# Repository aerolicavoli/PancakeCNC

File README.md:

# PancakeCNC

A fully custom, pancake-printing CNC platform. This repository collects the mechanical CAD, controller electronics, firmware, ground station tooling, and reference simulations that work together to lay down batter in precise paths.

## Table of Contents
- [Project Overview](#project-overview)
- [Repository Layout](#repository-layout)
- [Mechanical Platform](#mechanical-platform)
- [Electronics and PCB](#electronics-and-pcb)
- [Firmware (`Pancake_esp`)](#firmware-pancake_esp)
- [Ground Station Tools](#ground-station-tools)
- [Simulation & Analysis](#simulation--analysis)
- [Design Documentation](#design-documentation)
- [Command & Telemetry Protocol](#command--telemetry-protocol)
- [Development Environment](#development-environment)
- [License](#license)

## Project Overview
PancakeCNC is a learning platform for end-to-end mechatronics: mechanical design, PCB layout, embedded firmware, networking, and motion control. The goal is to dispense pancake batter using precise CNC motion profiles driven from a custom controller and cloud-connected command stream.

## Repository Layout
```
ControllerPCB/   KiCad project files for the controller board and manufacturing assets.
DesignDocs/      Engineering notes, diagrams, and BOMs.
GroundStation/   Python-based tooling for sending CNC commands and replaying G-code.
PancakeSim/      MATLAB scripts for kinematic studies and controller validation.
Pancake_esp/     ESP-IDF firmware for the ESP32-S3 based controller.
```

## Mechanical Platform
Motion is handled by a double-jointed planar arm that provides two rotational degrees of freedom so the dispenser can reach any point in the intended print envelope. Batter is metered with a peristaltic pump mounted at the arm's end effector.

The printable CAD for the hinges and pump assembly is currently tracked outside this repository; the focus here is on the control stack that drives the mechanism.

## Electronics and PCB
The `ControllerPCB` directory captures the KiCad design for the controller enclosure. Highlights include:

- ESP32-S3 compute module, GPIO breakout, and headers that feed external step/dir motor drivers sourced from the BOM.
- Power conditioning and 5 V level shifting for peripheral interfaces.
- Ready-to-fabricate assets: schematic (`ControllerPCB.kicad_sch`), layout (`ControllerPCB.kicad_pcb`), and generated BOM/gerbers.

## Firmware (`Pancake_esp`)
Firmware is built with ESP-IDF and lives under `Pancake_esp/`. Key modules:

- **Command Handling** (`CommandHandler.*`, `CNCOpCodes.h`): parses high-level instructions into motion primitives.
- **Motion Control** (`MotorControl.*`, `StepperMotor.*`, `TrapezoidalJog.*`, `ArchimedeanSpiral.*`): generates coordinated movements for the S0/S1 axes and pump.
- **Networking & Telemetry** (`InfluxDBCmdAndTlm.*`, `Telemetry.*`, `WifiHandler.*`): streams commands from InfluxDB and publishes runtime state.
- **Safety & UI** (`Safety.*`, `UI.*`): implements interlocks and emergency stop logic. A dedicated human interface is still a work in progress—commands flow through the InfluxDB bridge today.

To build the firmware you will need the ESP-IDF toolchain (v5.x recommended). After configuring credentials in `sdkconfig`/`Secret.h`, standard `idf.py build flash monitor` targets apply.

### Viewing ESP logs over the flash serial port (macOS)
The firmware keeps ESP-IDF logging active on the default serial sink, so anything emitted with `ESP_LOG*` can be viewed on the same USB serial device used for flashing.

1. List serial devices:
   ```bash
   ls /dev/cu.usb*
   ```
2. Open a monitor (replace the port with your device):
   ```bash
   idf.py -p /dev/cu.usbmodemXXXX monitor
   ```
   If you are outside an ESP-IDF shell, a simple fallback is:
   ```bash
   screen /dev/cu.usbmodemXXXX 115200
   ```
3. Exit monitor:
   - `idf.py monitor`: press `Ctrl+]`
   - `screen`: press `Ctrl+A`, then `K`, then `Y`

## Ground Station Tools
`GroundStation/CommandTerminal.py` is a CLI utility for sending commands through InfluxDB using a human-readable syntax. Example interactions:

```bash
python GroundStation/CommandTerminal.py e "Hello Pancake"
python GroundStation/CommandTerminal.py cnc_spiral CenterX_m=0.2 LinearSpeed_mps=0.05
python GroundStation/CommandTerminal.py run_file GroundStation/GCode/TestProgram.txt
```

Environment variables must be set to connect to InfluxDB:

- `INFLUXDB_URL`
- `INFLUXDB_TOKEN`
- `INFLUXDB_ORG`
- `INFLUXDB_CMD_BUCKET`

`GroundStation/GCode/` contains sample programs for testing complex pours.

## Simulation & Analysis
`PancakeSim/KinematicTestBed.m` is a MATLAB script for exercising the inverse kinematics and closed-loop control algorithms before they are deployed to hardware.

## Design Documentation
`DesignDocs/` aggregates system-level context:

- `DesignDiagrams.drawio` — block diagrams and signal flows.
- `BillOfMaterials.md` — hardware inventory and sourcing notes.
- `Channelization.md` — signal/channel mapping across subsystems.

## Command & Telemetry Protocol
Commands are binary packets exchanged through InfluxDB and consumed by the firmware.

### Frame Layout
| Byte Index | Field | Size | Description |
|------------|-------|------|-------------|
| `[0]` | **Op Code** | 1 byte | Instruction identifier |
| `[1]` | **Length** | 1 byte | Number of payload bytes (*n*) |
| `[2..n+1]` | **Payload** | *n* bytes | Instruction-specific data |

### Firmware Opcodes
Immediate commands bypass the CNC queue:

- `0x01` — `pause`
- `0x02` — `resume`
- `0x03` — `stop`
- `0x69` — `echo`

Queued motion & configuration commands include:

- `0x11` — `cnc_spiral`
- `0x12` — `cnc_jog`
- `0x13` — `wait`
- `0x14` — `cnc_sine`
- `0x15` — `cnc_constant_speed`
- `0x16` — `set_motor_limits`
- `0x17` — `set_pump_constant`
- `0x18` — `cnc_arc`
- `0x19` — `pump_purge`

Payloads are little-endian C structs (refer to headers under `Pancake_esp/main/`). The CLI automatically translates key-value inputs into the correct binary layouts. `pump_purge` accepts a signed `pumpSpeed_degps`; use a negative value, such as `pump_purge pumpSpeed_degps=-300 duration_ms=500`, to reverse the pump and pull batter back before stopping.

### Round-Trip Testing
`GroundStation/RoundtripTest.py` can send a command and fetch the recorded response, verifying connectivity and serialization. If environment variables are missing it will attempt to source `Secret.sh`.

## Development Environment
- **Firmware**: ESP-IDF (requires Python, CMake, Ninja). Install dependencies per Espressif documentation.
- **Ground Station**: Python 3.10+. Install requirements (if a `requirements.txt` is added) or run directly with the standard library and `influxdb-client`.
- **Mechanical/Electrical CAD**: KiCad 7.x for PCB edits, CAD/CAM packages for STL manipulation.

## License
This project is currently distributed without an explicit license; treat the assets as freely reusable unless noted otherwise in specific subdirectories.

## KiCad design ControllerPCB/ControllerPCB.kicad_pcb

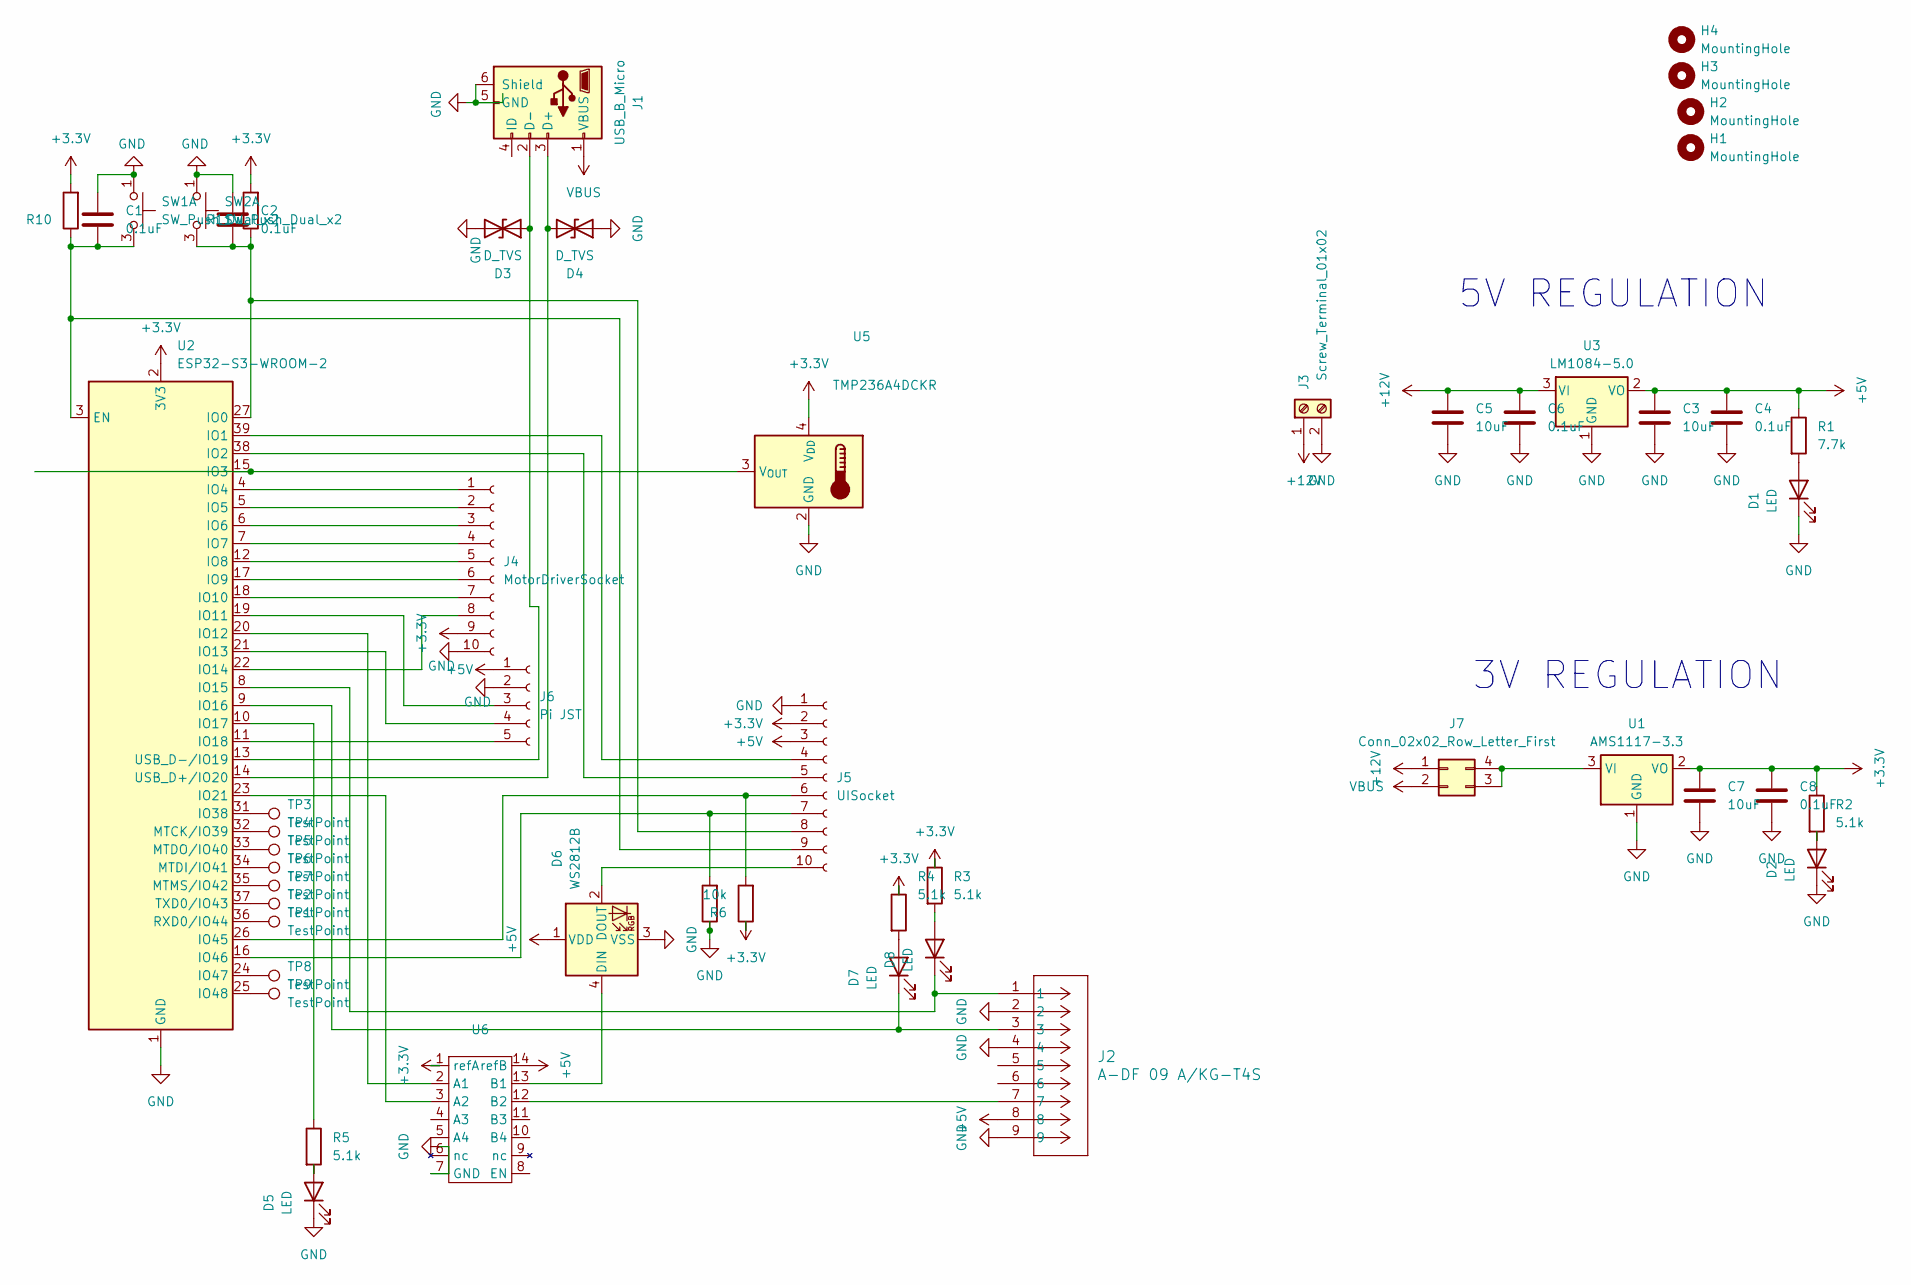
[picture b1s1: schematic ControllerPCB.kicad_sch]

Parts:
C1, C2, C4, C6, C8: 0.1uF; C_0805_2012Metric_Pad1.18x1.45mm_HandSolder
C3, C5, C7: 10uF; C_0805_2012Metric_Pad1.18x1.45mm_HandSolder
D1, D2, D5, D7, D8: LED; LED_0805_2012Metric_Pad1.15x1.40mm_HandSolder
D3, D4: D_TVS; D_SOD-323_HandSoldering
D6: WS2812B; LED_WS2812B_PLCC4_5.0x5.0mm_P3.2mm
H1, H2, H3, H4: MountingHole; MountingHole_3.2mm_M3
J1: USB_B_Micro; USB_Micro-AB_Molex_47590-0001
J2: A-DF 09 A/KG-T4S; MyDSUBASSMANN_A-DF_09_A_KG-T4S
J3: Screw_Terminal_01x02; TerminalBlock_TE_282834-2_1x02_P2.54mm_Horizontal
J4: MotorDriverSocket; 10JQ-BT_JST
J5: UISocket; 10JQ-BT_JST
J6: Pi JST; JST_EH_B5B-EH-A_1x05_P2.50mm_Vertical
J7: Conn_02x02_Row_Letter_First; PinSocket_2x02_P2.54mm_Vertical
R1: 7.7k; R_0805_2012Metric_Pad1.20x1.40mm_HandSolder
R2, R3, R4, R5: 5.1k; R_0805_2012Metric_Pad1.20x1.40mm_HandSolder
R6, R9, R10, R11: 10k; R_0805_2012Metric_Pad1.20x1.40mm_HandSolder
SW1, SW2: SW_Push_Dual_x2; SMT_FS
TP1, TP2, TP3, TP4, TP5, TP6, TP7, TP8, TP9: TestPoint; TestPoint_Pad_1.5x1.5mm
U1: AMS1117-3.3; SOT-223-3_TabPin2
U2: ESP32-S3-WROOM-2
U3: LM1084-5.0; TO-263-3_TabPin2
U5: TMP236A4DCKR; SOT-353_SC-70-5_Handsoldering
U6: TSSOP-14-1EP_4.4x5mm_P0.65mm

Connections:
+3.3V: C7.1, C8.1, J4.9, J5.2, R2.1, R3.1, R4.1, R6.1, R10.2, R11.2, U1.2 (VO), U2.2 (3V3), U5.4 (V_{DD}), U6.1 (refA)
+5V: C3.1, C4.1, D6.1 (VDD), J2.8, J5.3, J6.1, R1.1, U3.2 (VO), U6.14 (refB)
+12V: C5.1, C6.1, J3.1, J7.1 (Pin_a1), U3.3 (VI)
GND: C1.1, C2.1, C3.2, C4.2, C5.2, C6.2, C7.2, C8.2, D1.1 (K), D2.1 (K), D3.2 (A2), D4.1 (A1), D5.1 (K), D6.3 (VSS), J1.5 (GND), J1.6 (Shield), J2.2, J2.4, J2.9, J3.2, J4.10, J5.1, J6.2, R9.1, SW1.1 (C), SW2.1 (C), U1.1 (GND), U2.1 (GND), U2.40 (GND), U2.41 (GND), U3.1 (GND), U5.2 (GND), U5.5 (GND), U6.7 (GND)
unnamed: D1.2 (A), R1.2
unnamed: D2.2 (A), R2.2
unnamed: D3.1 (A1), J1.2 (D-), U2.13 (USB_D-/IO19)
unnamed: D4.2 (A2), J1.3 (D+), U2.14 (USB_D+/IO20)
unnamed: D5.2 (A), R5.2
unnamed: D6.4 (DIN), U6.13 (B1)
unnamed: D6.2 (DOUT), J5.10
unnamed 11: D7.2 (A), R4.2; also elsewhere on the board
unnamed 12: D7.1 (K), J2.3, U2.9 (IO16); also elsewhere on the board
unnamed 13: D8.2 (A), R3.2; also elsewhere on the board
unnamed 14: D8.1 (K), J2.1, U2.8 (IO15); also elsewhere on the board
unnamed: J4.1, U2.4 (IO4)
unnamed: J4.2, U2.5 (IO5)
unnamed: J4.3, U2.6 (IO6)
unnamed: J4.4, U2.7 (IO7)
unnamed: J4.5, U2.12 (IO8)
unnamed: J4.6, U2.17 (IO9)
unnamed: J4.7, U2.18 (IO10)
unnamed: J4.8, U2.22 (IO14)
unnamed: J5.4, U2.39 (IO1)
unnamed: J5.5, U2.38 (IO2)
unnamed: J5.6, R6.2, U2.26 (IO45)
unnamed: J5.7, R9.2, U2.16 (IO46)
unnamed: C2.2, J5.8, R11.1, SW2.3 (D), U2.27 (IO0)
unnamed: C1.2, J5.9, R10.1, SW1.3 (D), U2.3 (EN)
unnamed: J6.3, U2.19 (IO11)
unnamed: J6.4, U2.21 (IO13)
unnamed: J6.5, U2.11 (IO18)
unnamed: J7.3 (Pin_b2), J7.4 (Pin_b1), U1.3 (VI)
unnamed: U2.15 (IO3), U5.3 (V_{OUT})
unnamed: U2.20 (IO12), U6.2 (A1)
unnamed: R5.1, U2.10 (IO17)
unnamed: U2.23 (IO21), U6.3 (A2)
unnamed: TP3.1, U2.31 (IO38)
unnamed: TP8.1, U2.24 (IO47)
unnamed: TP9.1, U2.25 (IO48)
unnamed: TP4.1, U2.32 (MTCK/IO39)
unnamed: TP6.1, U2.34 (MTDI/IO41)
unnamed: TP5.1, U2.33 (MTDO/IO40)
unnamed: TP7.1, U2.35 (MTMS/IO42)
unnamed: TP1.1, U2.36 (RXD0/IO44)
unnamed: TP2.1, U2.37 (TXD0/IO43)
unnamed: J2.7, U6.12 (B2)
VBUS: J1.1 (VBUS), J7.2 (Pin_a2)

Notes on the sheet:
5V REGULATION
3V REGULATION

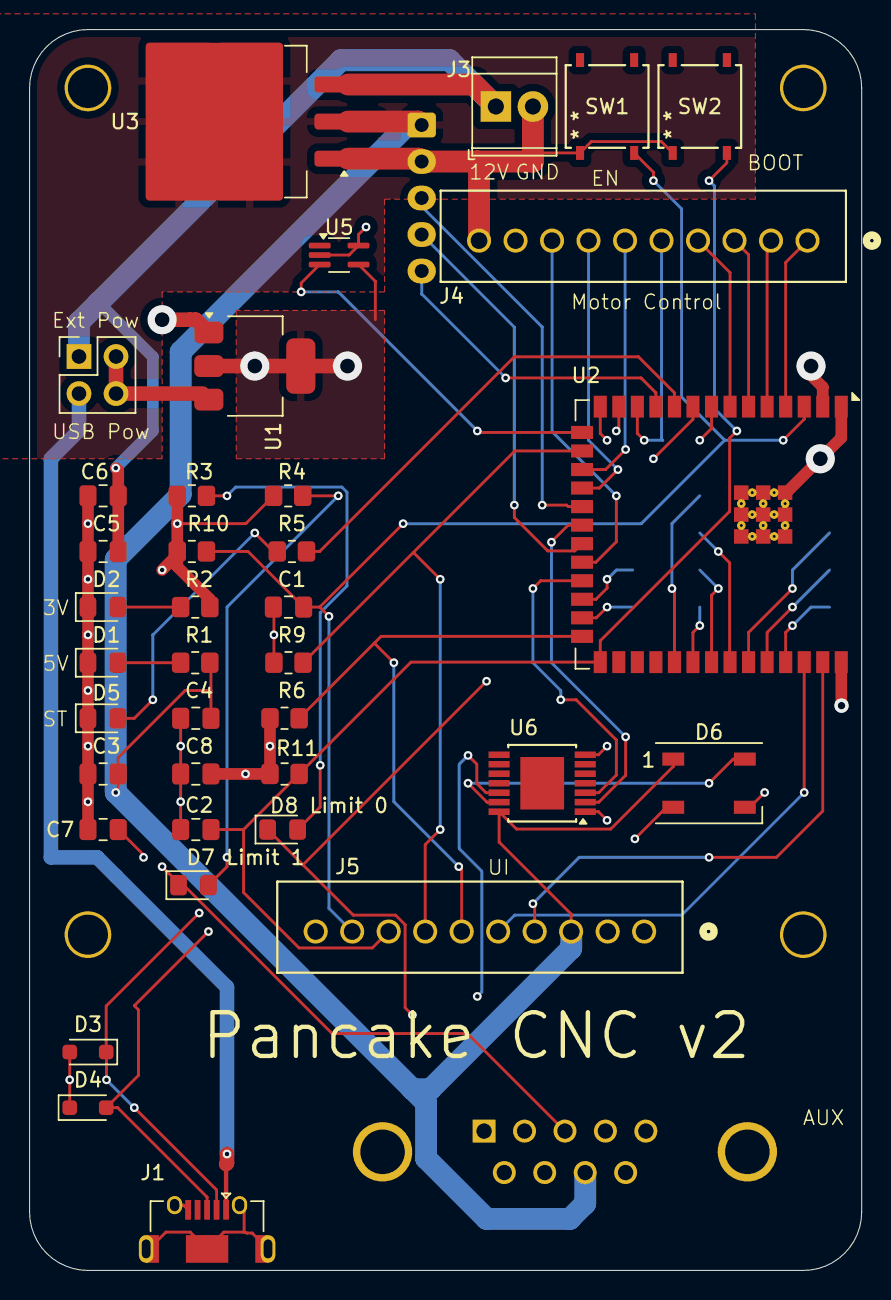
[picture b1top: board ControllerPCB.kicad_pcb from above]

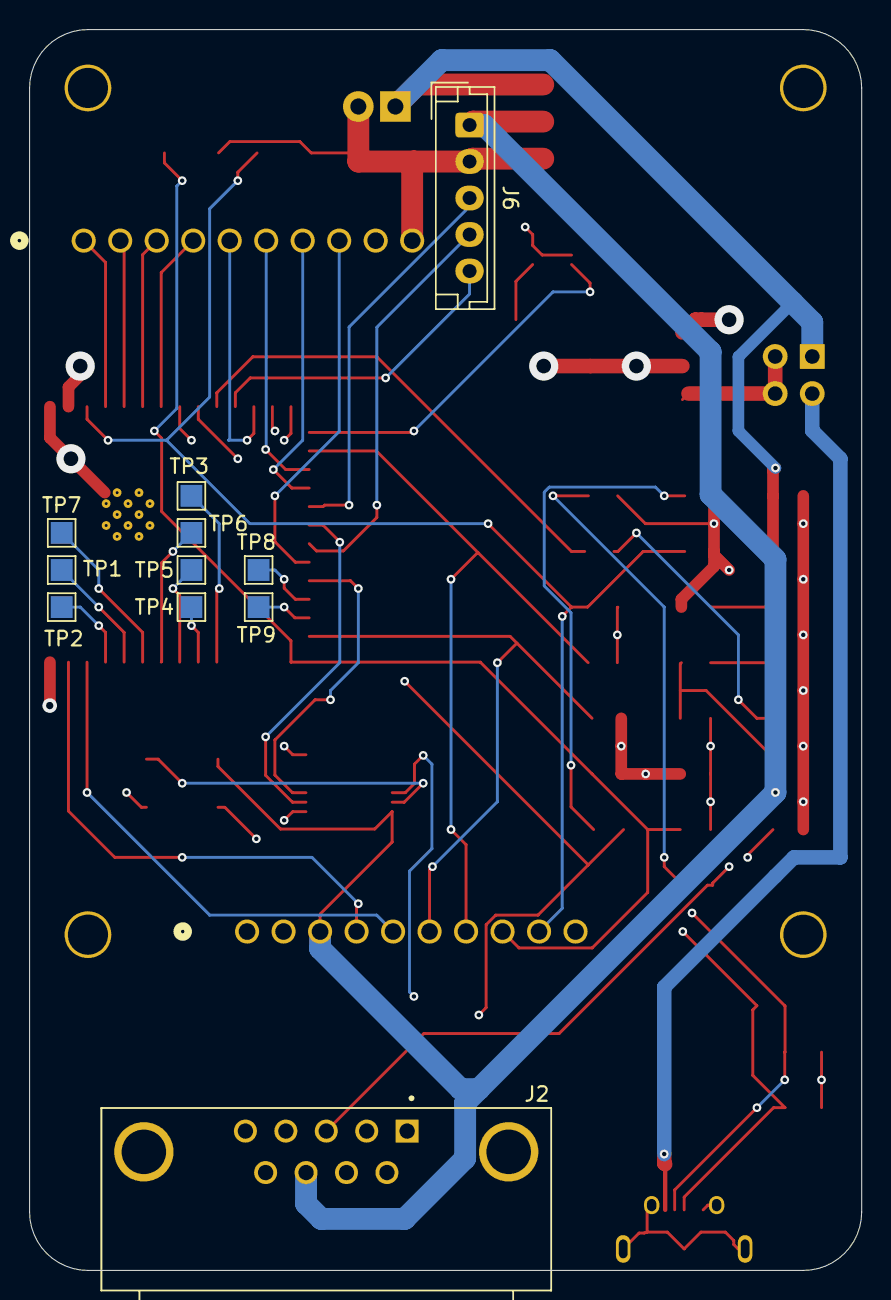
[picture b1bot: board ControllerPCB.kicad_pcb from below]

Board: 4 copper layers, 57.0 x 85.0 mm, 52 parts (11 on the bottom side), 48 nets.

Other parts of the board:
D7 Limit 1, D8 Limit 0: LED; LED_0805_2012Metric_Pad1.15x1.40mm_HandSolder

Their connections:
unnamed 11: D7 Limit 1.2 (A); also elsewhere on the board
unnamed 12: D7 Limit 1.1 (K); also elsewhere on the board
unnamed 13: D8 Limit 0.2 (A); also elsewhere on the board
unnamed 14: D8 Limit 0.1 (K); also elsewhere on the board

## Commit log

2024-11-08 Initial check in. Basic motor control functionality and experimental serial interface
2024-11-08 Update serial config
2024-11-08 Add escape characters to the message payload to avoid stomping on sync word
2024-11-08 Rework serial parsing to a state machine arc
2024-11-08 Fix cksum, remove length and type
2024-11-08 Fixed pi to esp32 cmd bug
2024-11-10 Motor control dev
2024-11-16 Check in first rev of controller pcb
2024-11-17 Rev 2 of controller PCB
2024-11-17 Initial pancake sim check in
2024-11-17 Configure the limit switches
2024-11-17 Setup motor enable / disable commanding and limit switch handling
2024-11-17 Initial UI check in
2024-11-18 Implement temperature sensing
2024-12-15 Initial guidance and geometry controls
2024-12-15 Check in tlm publisher
2024-12-15 Repo Cleanup
2024-12-28 Tlm Publisher can now connect to influx
2025-05-24 Add raw logging capability to PI UI
2025-05-24 Add raw logging capability to PI UI V2
2025-05-24 Wifi and time sync works. Transmiting to influx does not.
2025-05-25 Can log data and all logs to influx
2025-05-26 Setup CNC state machine, spirals, and jogs
2025-05-26 Update buildspec for motor control
2025-05-26 Logging works well, Sprialing a pancake
2025-05-26 Progress save. Bug in motor control or pan math. CNC out of bounds error
2025-06-02 Can no longer sprial. Memory issue in how instruction set is configured, used
2025-06-02 Format cleanup
2025-06-15 Update program control structure to message stream
2025-06-15 Correct enable pin hadling and publish limit switch tlm
2025-06-24 Sprials 2 pancakes. Ready for system test
2025-06-26 Added in pump control, cleanup
2025-06-27 Code cleanup
2025-07-05 Create sine CNC guidance to debug steppers
2025-07-05 Cleanup includes
2025-07-12 Add homing capabilities, zeroing, constant angle rate commands
2025-07-29 Bug fixes and tuning from system test
2025-07-30 Remove TlmPublisher AI slop. Refactor and setup framework for influxdb based commanding
2025-07-31 Sometimes connects to wifi before crashing
2025-07-31 Add bounds checks for UART protocol
2025-08-23 Progress Save, non functional wifi
2025-08-24 Removed erroneous esp_error check, left modem power saving state a default
2025-08-24 Wifi connects and tlm logs to influx
2025-09-01 Reliable internet, querey and transmition work
2025-09-02 Querey functions, parsing does not
2025-09-02 Handle blank lines in InfluxDB response
2025-09-02 Fix and centralize InfluxDB CSV parsing
2025-09-02 Implement portable UTC time conversion
2025-09-02 Initialize command queue for InfluxDB handler
2025-09-02 Implement queue-driven command handler
2025-09-02 Tidy logging and add command help
2025-09-02 Human touch to an evening of codex
2025-09-13 Restore Safety features
2025-09-13 Local repo cleanup
2025-09-13 Check in progress towards finishing influxdb commanding interface
2025-09-13 Check in readme
2025-09-13 docs: tidy README
2025-09-13 Progress save, remote commanding works great
2025-09-14 Prompt engineering at its finest, works great
2025-09-14 Nearly ready for wet dress rehersal
2025-09-14 System debugging
2025-09-15 feat: log command acknowledgements
2025-09-15 fix: declare AddCmdAckToBuffer
2025-09-15 fix: make command terminal interactive
2025-09-15 refactor: simplify command terminal
2025-09-15 feat: show logs and command acks in terminal
2025-09-16 Remove PiUI interface and centralize telemetry data
2025-09-17 Wrap motor angle commands to shortest path
2025-09-17 Fix build errors, check in pump flow gcode
2025-09-17 Zero-initialize HTTP client config structs
2025-09-17 Refactor CNC opcode handling
2025-09-17 Add Tkinter run file designer application
2025-09-20 Expose accel scale command in terminal
2025-10-18 CNC functions well, adding in docs
2025-10-18 Clean up repo
2025-10-18 docs: align readme with current hardware
2026-04-26 Keep ESP logs on serial while mirroring to telemetry
2026-05-24 progress save
2026-05-24 Add rectangle guidance command
2026-06-04 Add tests
2026-06-04 Expand tests
2026-06-04 Fix out of bounds logic
2026-06-04 Go to angle
2026-06-06 Reversable pump
2026-06-06 Add pump rev
2026-06-06 Check in plan
2026-06-20 Limiting logic working better
2026-06-20 Works ok, stop reboot persists
2026-06-21 New gcode and features
2026-06-21 Add local origin and multi-pattern run files
2026-06-21 Support nested run files in visualizer
2026-06-21 Generalize telemetry rate registry
2026-06-21 Document telemetry bandwidth budget
2026-06-21 Work logo working ok
2026-06-30 Works well
